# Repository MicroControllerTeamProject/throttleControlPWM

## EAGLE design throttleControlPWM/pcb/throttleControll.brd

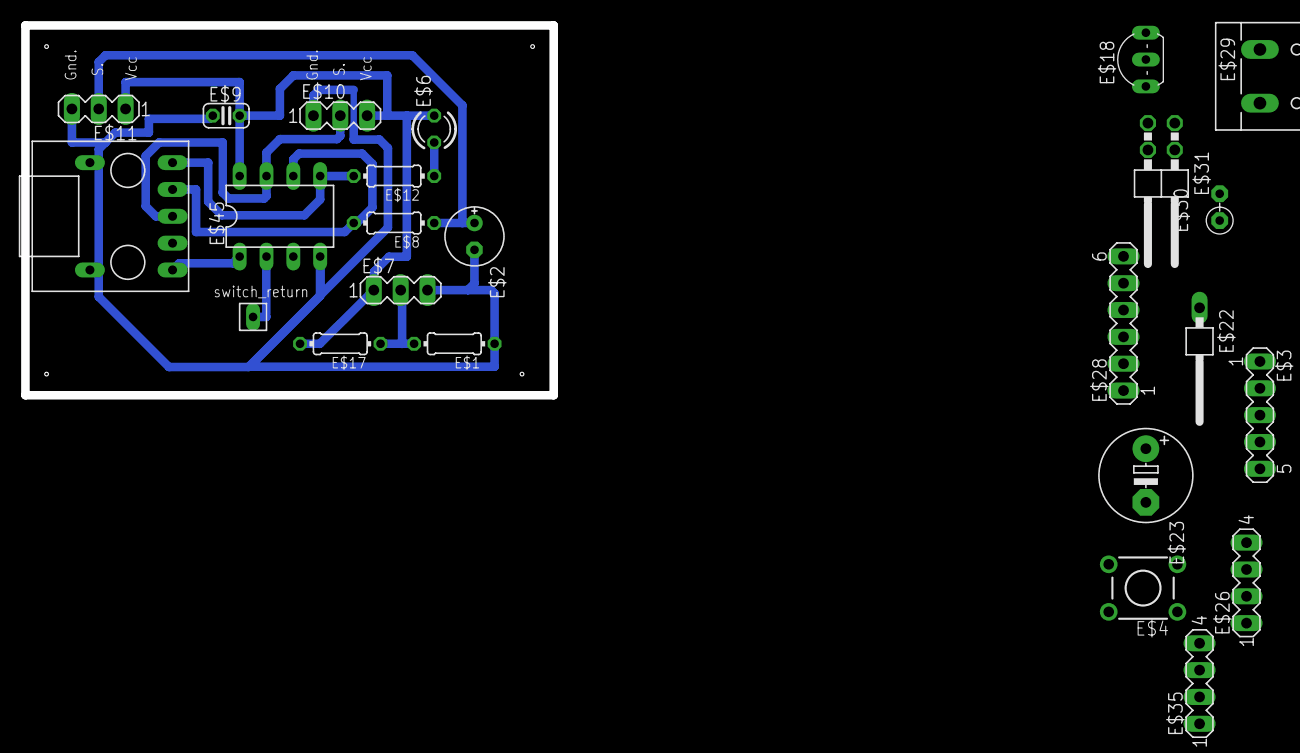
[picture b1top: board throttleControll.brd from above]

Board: 2 copper layers, 50.0 x 35.0 mm, 24 parts (0 on the bottom side), 10 nets.

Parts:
E$1: 10k; 0204/7
E$2: 10uF; E2,5-6E
E$3: MA05-1
E$4: TL1105
E$5: USB-MICRO-PCB
E$6: Led; LED3MM
E$7: switch; MA03-1
E$8: 5k; 0204/7
E$9: 1uF; C025-024X044
E$10: throttle; MA03-1
E$11: hub; MA03-1
E$12: 220; 0204/7
E$13: FE01-1
E$17: 19k; 0204/7
E$18: TO92-
E$22: 1X01/90
E$23: E5-8,5
E$26, E$35: MA04-1
E$28: MA06-1
E$29: W237-132
E$30: RS-2,5
E$31: 2X02/90
E$45: DIL08

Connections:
MOSI: E$5.P$1, E$12.2, E$45.5
S$2: E$6.K, E$7.1, E$9.2, E$10.3, E$11.1, E$17.2, E$45.8
S$3: E$1.2, E$7.2, E$17.1
S$4: E$1.1, E$2.-, E$5.P$6, E$7.3, E$9.1, E$10.1, E$11.3, E$45.4
S$5: E$2.+, E$8.1, E$11.2
S$7: E$6.A, E$12.1
S$9: E$5.P$3, E$10.2, E$45.7
S$11: E$5.P$2, E$8.2, E$45.6
S$12: E$5.P$5, E$45.1
S$13: E$13.1, E$45.2
